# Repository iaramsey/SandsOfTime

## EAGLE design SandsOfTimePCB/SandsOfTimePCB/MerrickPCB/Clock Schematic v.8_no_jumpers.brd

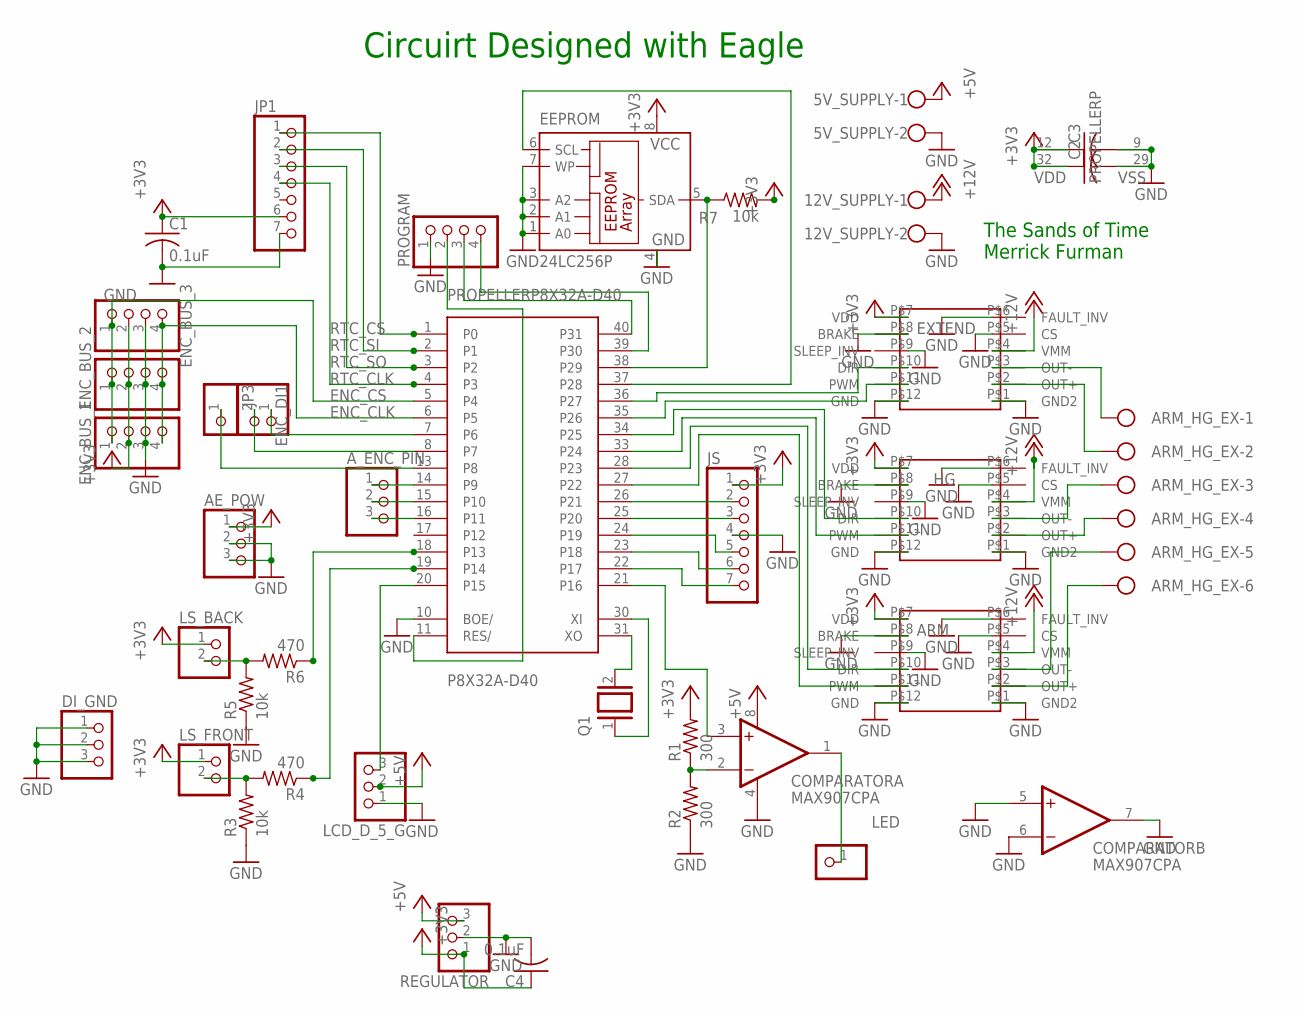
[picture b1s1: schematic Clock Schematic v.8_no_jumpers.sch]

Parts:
5V_SUPPLY, 12V_SUPPLY: W237-102
AE_POW: PINHD-1X3; 1X03
ARM: DRV
ARM_HG_EX: W237-6
A_ENC_PIN: PINHD-1X3; 1X03
C1: 0.1uF; C050-025X075
C2, C3: C-US050-025X075; C050-025X075
C4: 0.1uF; C025-030X050
COMPARATOR: MAX907CPA; DIL08
DI_GND: PINHD-1X3; 1X03
EEPROM: 24LC256P; DIL8
ENC_BUS_1, ENC_BUS_2, ENC_BUS_3: PINHD-1X4; 1X04
ENC_DI1: PINHD-1X2; 1X02
EXTEND: DRV
HG: DRV
JP1: PINHD-1X7; 1X07
JP3: PINHD-1X1; 1X01
JS: PINHD-1X7; 1X07
LCD_D_5_G: PINHD-1X3; 1X03
LED: PINHD-1X1; 1X01
LS_BACK: PINHD-1X2; 1X02
LS_FRONT: PINHD-1X2; 1X02
PROGRAM: PINHD-1X4; 1X04
PROPELLER: P8X32A-D40
Q1: XTAL/S; QS
R1, R2: 300; 0207/10
R3, R5, R7: 10k; 0207/10
R4, R6: 470; 0207/10
REGULATOR: PINHD-1X3; 1X03

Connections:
+3V3: AE_POW.1, ARM.P$7 (VDD), C1.1, C2.1, C3.1, C4.1, EEPROM.8 (VCC), ENC_BUS_1.2, ENC_BUS_2.2, ENC_BUS_3.2, EXTEND.P$7 (VDD), HG.P$7 (VDD), JP1.6, JS.1, LS_BACK.1, LS_FRONT.1, PROPELLER.12 (VDD), PROPELLER.32 (VDD), R1.2, R7.2, REGULATOR.1
+5V: 5V_SUPPLY.1, COMPARATOR.8 (V+), LCD_D_5_G.2, REGULATOR.3
+12V: 12V_SUPPLY.1, ARM.P$4 (VMM), EXTEND.P$4 (VMM), HG.P$4 (VMM)
ENC_CLK: ENC_BUS_1.4, ENC_BUS_2.4, ENC_BUS_3.4, PROPELLER.6 (P5)
ENC_CS: ENC_BUS_1.1, ENC_BUS_2.1, ENC_BUS_3.1, PROPELLER.5 (P4)
GND: 5V_SUPPLY.2, 12V_SUPPLY.2, AE_POW.2, AE_POW.3, ARM.P$1 (GND2), ARM.P$5 (CS), ARM.P$6 (FAULT_INV), ARM.P$8 (BRAKE), ARM.P$9 (SLEEP_INV), ARM.P$12 (GND), C1.2, C2.2, C3.2, C4.2, COMPARATOR.4 (V-), COMPARATOR.5 (+IN), COMPARATOR.6 (-IN), COMPARATOR.7 (OUT), DI_GND.1, DI_GND.2, DI_GND.3, EEPROM.1 (A0), EEPROM.2 (A1), EEPROM.3 (A2), EEPROM.4 (GND), EEPROM.7 (WP), ENC_BUS_1.3, ENC_BUS_2.3, ENC_BUS_3.3, EXTEND.P$1 (GND2), EXTEND.P$5 (CS), EXTEND.P$6 (FAULT_INV), EXTEND.P$8 (BRAKE), EXTEND.P$9 (SLEEP_INV), EXTEND.P$12 (GND), HG.P$1 (GND2), HG.P$5 (CS), HG.P$6 (FAULT_INV), HG.P$8 (BRAKE), HG.P$9 (SLEEP_INV), HG.P$12 (GND), JP1.7, JS.4, LCD_D_5_G.1, PROGRAM.1, PROPELLER.9 (VSS), PROPELLER.10 (BOE/), PROPELLER.29 (VSS), R2.1, R3.1, R5.1, REGULATOR.2
unnamed: ENC_DI1.1, PROPELLER.7 (P6)
unnamed: JS.5, PROPELLER.24 (P19)
unnamed: JS.6, PROPELLER.23 (P18)
unnamed: JS.7, PROPELLER.22 (P17)
unnamed: JS.3, PROPELLER.25 (P20)
unnamed: JS.2, PROPELLER.26 (P21)
unnamed: LCD_D_5_G.3, PROPELLER.20 (P15)
unnamed: ENC_DI1.2, PROPELLER.8 (P7)
unnamed: COMPARATOR.1 (OUT), LED.1
unnamed: PROPELLER.31 (XO), Q1.2
unnamed: COMPARATOR.2 (-IN), R1.1, R2.2
unnamed: PROPELLER.30 (XI), Q1.1
unnamed: PROPELLER.19 (P14), R4.1
unnamed: LS_BACK.2, R5.2, R6.2
unnamed: PROPELLER.18 (P13), R6.1
unnamed: EEPROM.6 (SCL), PROPELLER.37 (P28)
unnamed: ARM.P$11 (PWM), PROPELLER.27 (P22)
unnamed: PROGRAM.4, PROPELLER.39 (P30)
unnamed: PROGRAM.3, PROPELLER.40 (P31)
unnamed: EEPROM.5 (SDA), PROPELLER.38 (P29), R7.1
unnamed: COMPARATOR.3 (+IN), PROPELLER.21 (P16)
unnamed: ARM.P$10 (DIR), PROPELLER.28 (P23)
unnamed: HG.P$11 (PWM), PROPELLER.33 (P24)
unnamed: HG.P$10 (DIR), PROPELLER.34 (P25)
unnamed: EXTEND.P$11 (PWM), PROPELLER.35 (P26)
unnamed: PROGRAM.2, PROPELLER.11 (RES/)
unnamed: LS_FRONT.2, R3.2, R4.2
unnamed: EXTEND.P$10 (DIR), PROPELLER.36 (P27)
unnamed: ARM_HG_EX.1, EXTEND.P$3 (OUT-)
unnamed: ARM_HG_EX.2, EXTEND.P$2 (OUT+)
unnamed: ARM_HG_EX.3, HG.P$3 (OUT-)
unnamed: ARM_HG_EX.4, HG.P$2 (OUT+)
unnamed: ARM.P$3 (OUT-), ARM_HG_EX.5
unnamed: ARM.P$2 (OUT+), ARM_HG_EX.6
unnamed: JP3.1, PROPELLER.13 (P8)
unnamed: A_ENC_PIN.1, PROPELLER.14 (P9)
unnamed: A_ENC_PIN.2, PROPELLER.15 (P10)
unnamed: A_ENC_PIN.3, PROPELLER.16 (P11)
RTC_CLK: JP1.4, PROPELLER.4 (P3)
RTC_CS: JP1.1, PROPELLER.1 (P0)
RTC_SI: JP1.2, PROPELLER.2 (P1)
RTC_SO: JP1.3, PROPELLER.3 (P2)

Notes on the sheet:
The Sands of Time Merrick Furman
Circuirt Designed with Eagle

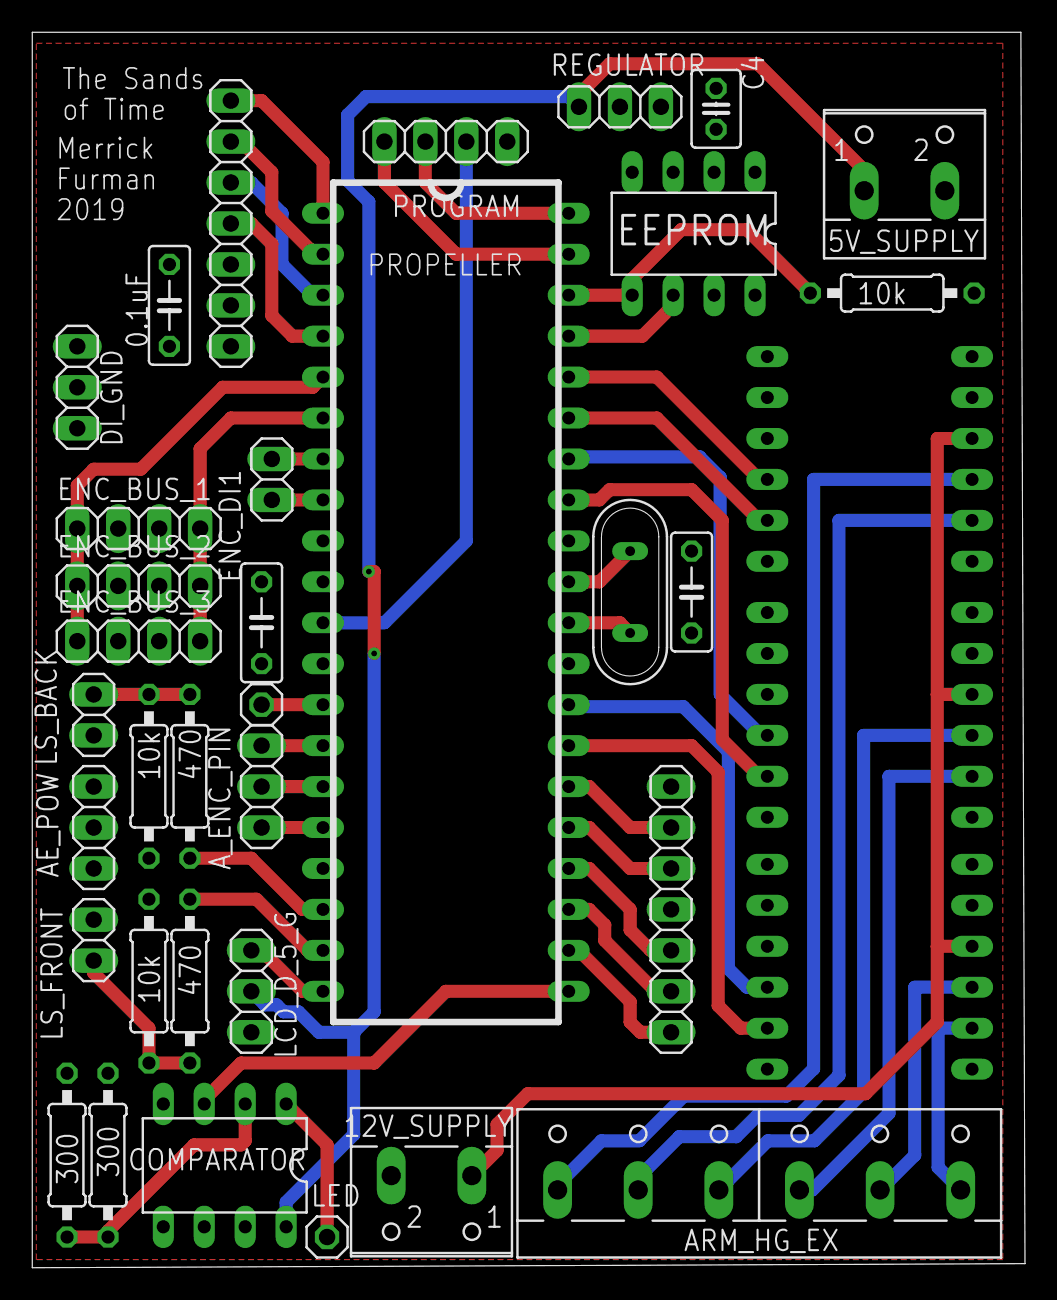
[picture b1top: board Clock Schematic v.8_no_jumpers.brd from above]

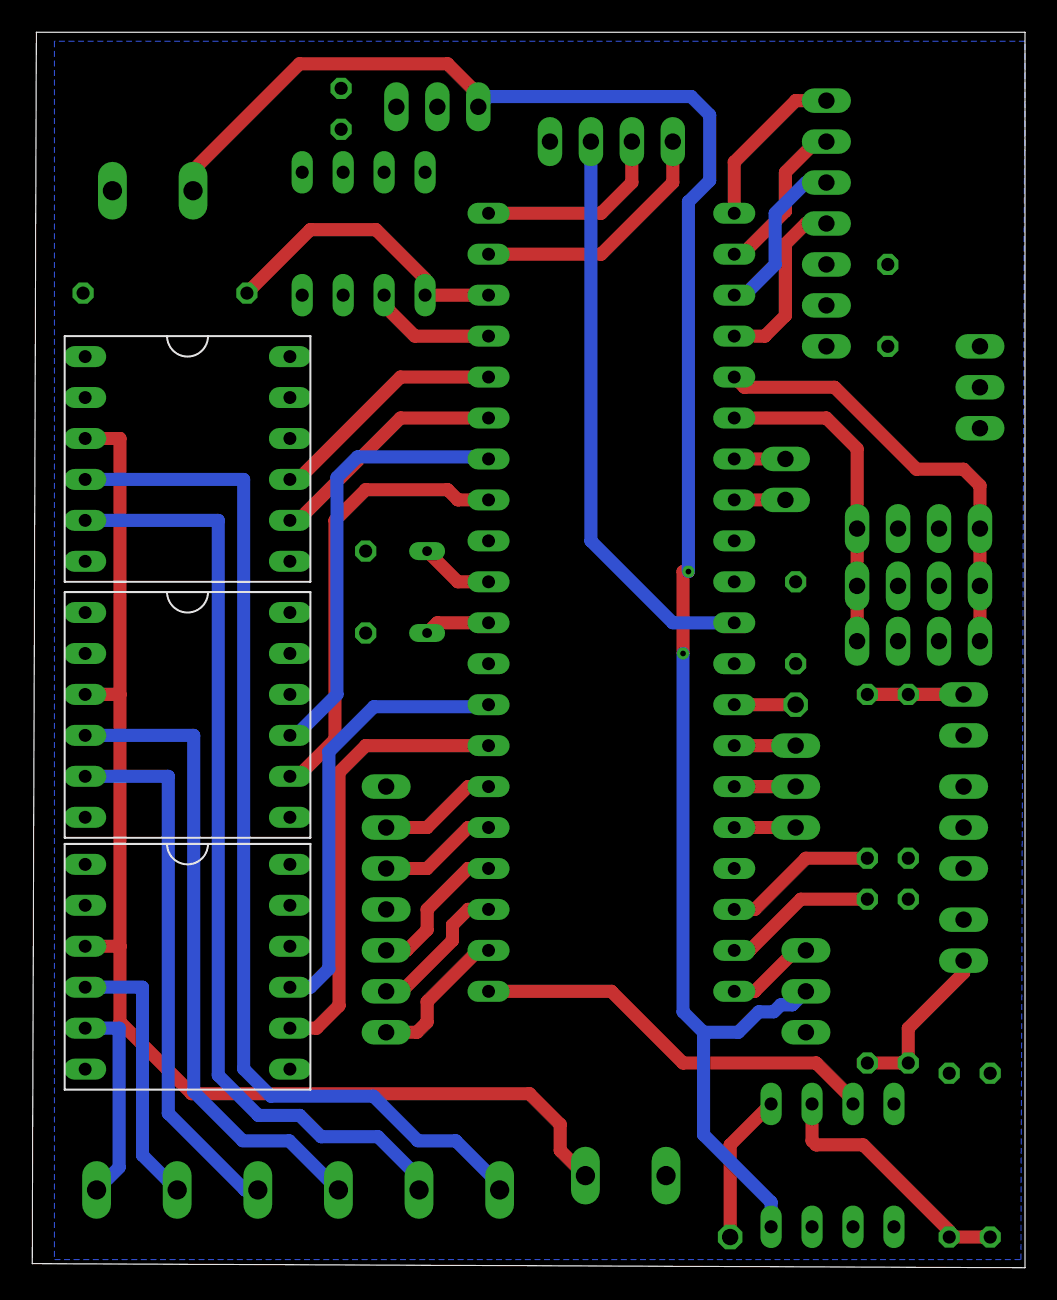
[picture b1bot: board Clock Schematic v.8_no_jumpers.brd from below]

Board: 2 copper layers, 61.6 x 76.6 mm, 37 parts (3 on the bottom side), 48 nets.

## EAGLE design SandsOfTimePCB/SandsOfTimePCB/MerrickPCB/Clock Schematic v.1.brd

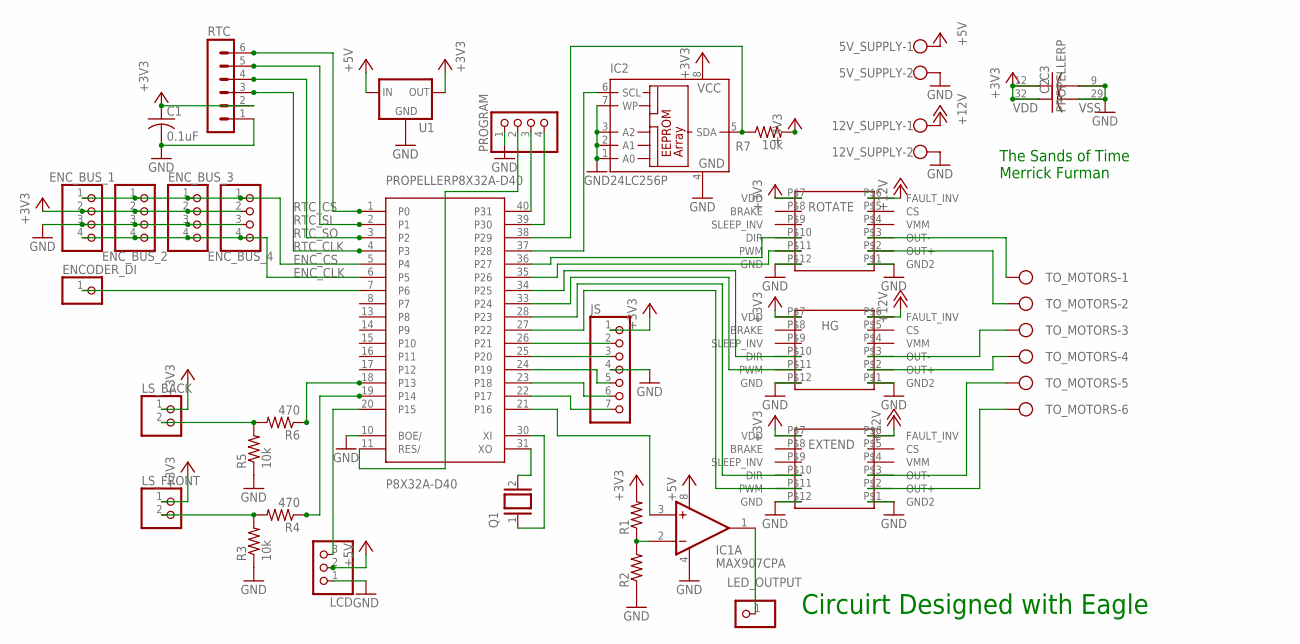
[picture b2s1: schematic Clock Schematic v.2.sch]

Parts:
5V_SUPPLY, 12V_SUPPLY: W237-102
C1: 0.1uF; C050-025X075
C2, C3: C-US050-025X075; C050-025X075
ENCODER_DI: PINHD-1X1; 1X01
ENC_BUS_1, ENC_BUS_2, ENC_BUS_3, ENC_BUS_4: PINHD-1X4; 1X04
EXTEND: DRV
HG: DRV
IC1: MAX907CPA; DIL08
IC2: 24LC256P; DIL8
JS: PINHD-1X7; 1X07
LCD: PINHD-1X3; 1X03
LED_OUTPUT: PINHD-1X1; 1X01
LS_BACK: PINHD-1X2; 1X02
LS_FRONT: PINHD-1X2; 1X02
PROGRAM: PINHD-1X4; 1X04
PROPELLER: P8X32A-D40
Q1: XTAL/S; QS
R1, R2: R-US_0207/10; 0207/10
R3, R5, R7: 10k; 0207/10
R4, R6: 470; 0207/10
ROTATE: DRV
RTC: MA06-1
TO_MOTORS: W237-6
U1: V_REG_78XXSIDE; 78XXL

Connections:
+3V3: C1.1, C2.1, C3.1, ENC_BUS_1.2, ENC_BUS_2.2, ENC_BUS_3.2, ENC_BUS_4.2, EXTEND.P$7 (VDD), HG.P$7 (VDD), IC2.8 (VCC), JS.1, LS_BACK.1, LS_FRONT.1, PROPELLER.12 (VDD), PROPELLER.32 (VDD), R1.2, R7.2, ROTATE.P$7 (VDD), RTC.2, U1.OUT
+5V: 5V_SUPPLY.1, IC1.8 (V+), LCD.2, U1.IN
+12V: 12V_SUPPLY.1, EXTEND.P$6 (FAULT_INV), HG.P$6 (FAULT_INV), ROTATE.P$6 (FAULT_INV)
ENC_CLK: ENC_BUS_1.4, ENC_BUS_2.4, ENC_BUS_3.4, ENC_BUS_4.4, PROPELLER.6 (P5)
ENC_CS: ENC_BUS_1.1, ENC_BUS_2.1, ENC_BUS_3.1, ENC_BUS_4.1, PROPELLER.5 (P4)
GND: 5V_SUPPLY.2, 12V_SUPPLY.2, C1.2, C2.2, C3.2, ENC_BUS_1.3, ENC_BUS_2.3, ENC_BUS_3.3, ENC_BUS_4.3, EXTEND.P$1 (GND2), EXTEND.P$12 (GND), HG.P$1 (GND2), HG.P$12 (GND), IC1.4 (V-), IC2.1 (A0), IC2.2 (A1), IC2.3 (A2), IC2.4 (GND), IC2.7 (WP), JS.4, LCD.1, PROGRAM.1, PROPELLER.9 (VSS), PROPELLER.10 (BOE/), PROPELLER.29 (VSS), R2.1, R3.1, R5.1, ROTATE.P$1 (GND2), ROTATE.P$12 (GND), RTC.1, U1.GND
unnamed: ENCODER_DI.1, PROPELLER.7 (P6)
unnamed: JS.5, PROPELLER.24 (P19)
unnamed: JS.6, PROPELLER.23 (P18)
unnamed: JS.7, PROPELLER.22 (P17)
unnamed: JS.3, PROPELLER.25 (P20)
unnamed: JS.2, PROPELLER.26 (P21)
unnamed: LCD.3, PROPELLER.20 (P15)
unnamed: IC1.3 (+IN), PROPELLER.21 (P16)
unnamed: IC1.1 (OUT), LED_OUTPUT.1
unnamed: PROPELLER.31 (XO), Q1.2
unnamed: IC1.2 (-IN), R1.1, R2.2
unnamed: PROPELLER.30 (XI), Q1.1
unnamed: PROPELLER.19 (P14), R4.1
unnamed: LS_BACK.2, R5.2, R6.2
unnamed: PROPELLER.18 (P13), R6.1
unnamed: IC2.6 (SCL), PROPELLER.37 (P28)
unnamed: EXTEND.P$11 (PWM), PROPELLER.27 (P22)
unnamed: PROGRAM.4, PROPELLER.39 (P30)
unnamed: PROGRAM.3, PROPELLER.40 (P31)
unnamed: IC2.5 (SDA), PROPELLER.38 (P29), R7.1
unnamed: EXTEND.P$10 (DIR), PROPELLER.28 (P23)
unnamed: HG.P$11 (PWM), PROPELLER.33 (P24)
unnamed: HG.P$10 (DIR), PROPELLER.34 (P25)
unnamed: PROPELLER.35 (P26), ROTATE.P$11 (PWM)
unnamed: PROGRAM.2, PROPELLER.11 (RES/)
unnamed: LS_FRONT.2, R3.2, R4.2
unnamed: PROPELLER.36 (P27), ROTATE.P$10 (DIR)
unnamed: ROTATE.P$3 (OUT-), TO_MOTORS.1
unnamed: ROTATE.P$2 (OUT+), TO_MOTORS.2
unnamed: HG.P$3 (OUT-), TO_MOTORS.3
unnamed: HG.P$2 (OUT+), TO_MOTORS.4
unnamed: EXTEND.P$3 (OUT-), TO_MOTORS.5
unnamed: EXTEND.P$2 (OUT+), TO_MOTORS.6
RTC_CLK: PROPELLER.4 (P3), RTC.3
RTC_CS: PROPELLER.1 (P0), RTC.6
RTC_SI: PROPELLER.2 (P1), RTC.5
RTC_SO: PROPELLER.3 (P2), RTC.4

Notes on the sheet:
The Sands of Time Merrick Furman
Circuirt Designed with Eagle

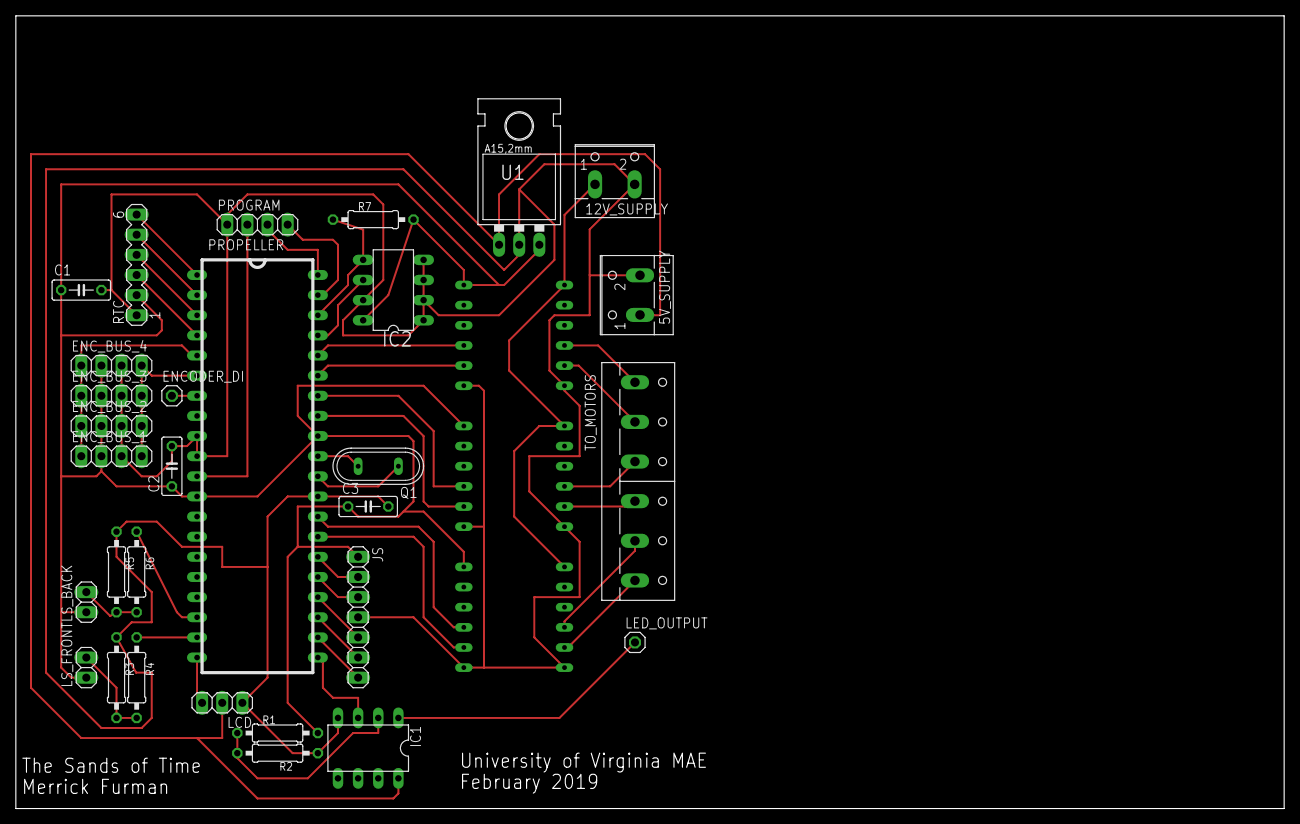
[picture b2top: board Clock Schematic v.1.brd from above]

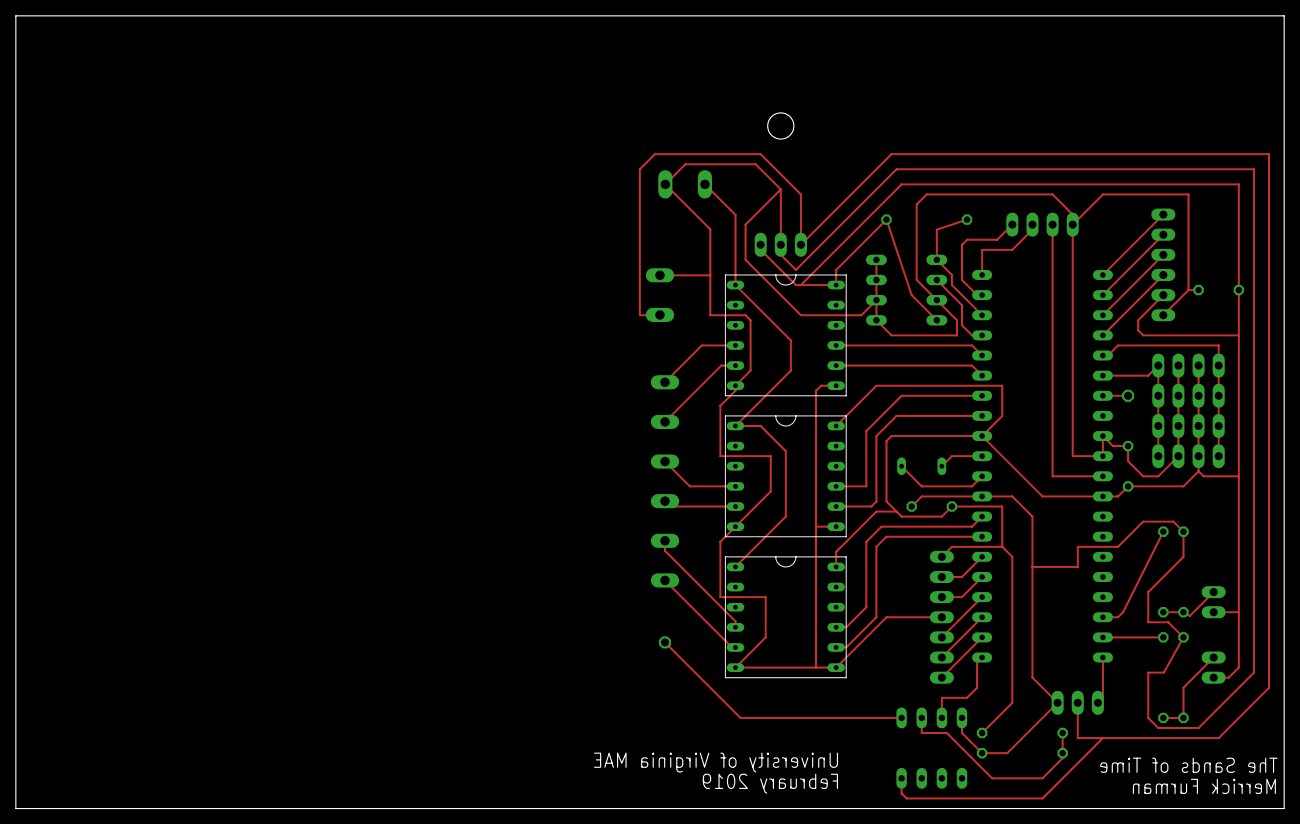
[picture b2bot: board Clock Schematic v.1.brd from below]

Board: 2 copper layers, 160.0 x 100.0 mm, 33 parts (3 on the bottom side), 43 nets.

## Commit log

2023-02-20 added kicad files
2023-03-15 added files from old project
2023-03-15 Hudson stuff
2023-03-20 Structure and Garner code
2023-03-22 finished DS3234 and motor drivers code
2023-03-29 So much things
2023-04-12 A whole lotta stuff
2023-05-01 worked on testing LCD
2023-05-02 added LED code to turn white for the hourglass being rotated
2023-05-03 Temporary
2023-05-03 removal of outa. ina. and dira.
2023-05-03 comments?
2023-05-06 cleanup
2023-05-11 Working demos

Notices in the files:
parts and their libraries:
SparkFun-IC-Power: Licensing: Creative Commons ShareAlike 4.0 International - https://creativecommons.org/licenses/by-sa/4.0
